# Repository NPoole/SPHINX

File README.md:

# SPHINX
Project to reproduce the Russian СФИНКС home computer concept

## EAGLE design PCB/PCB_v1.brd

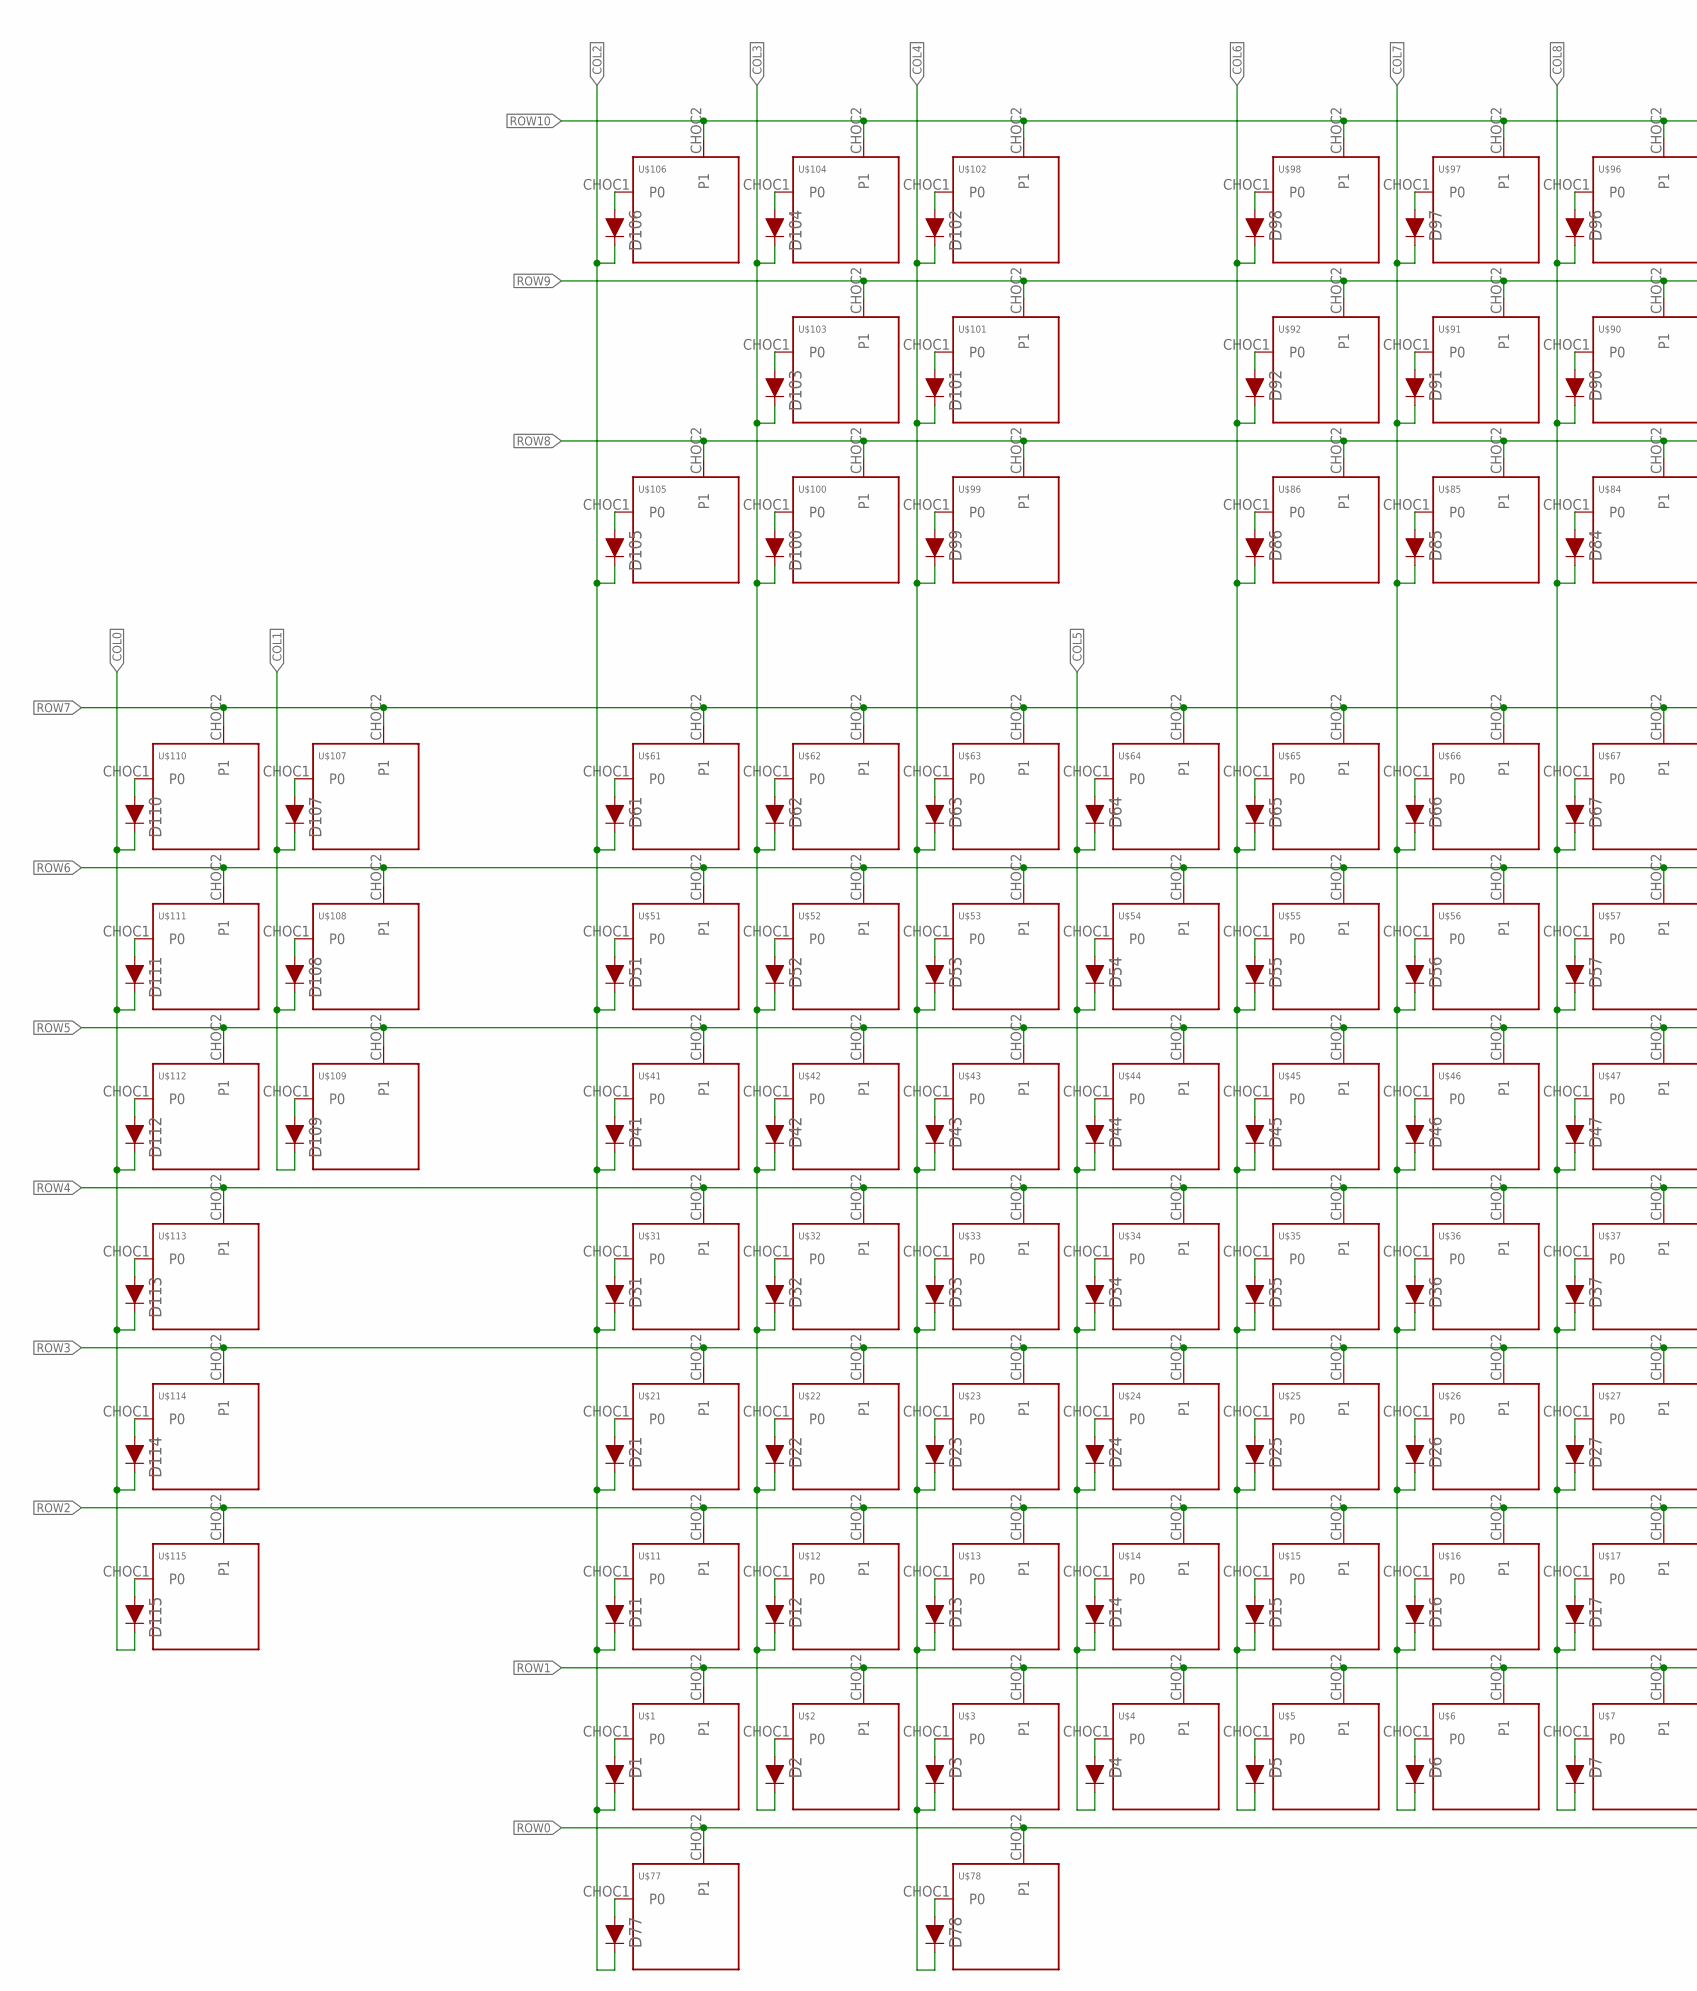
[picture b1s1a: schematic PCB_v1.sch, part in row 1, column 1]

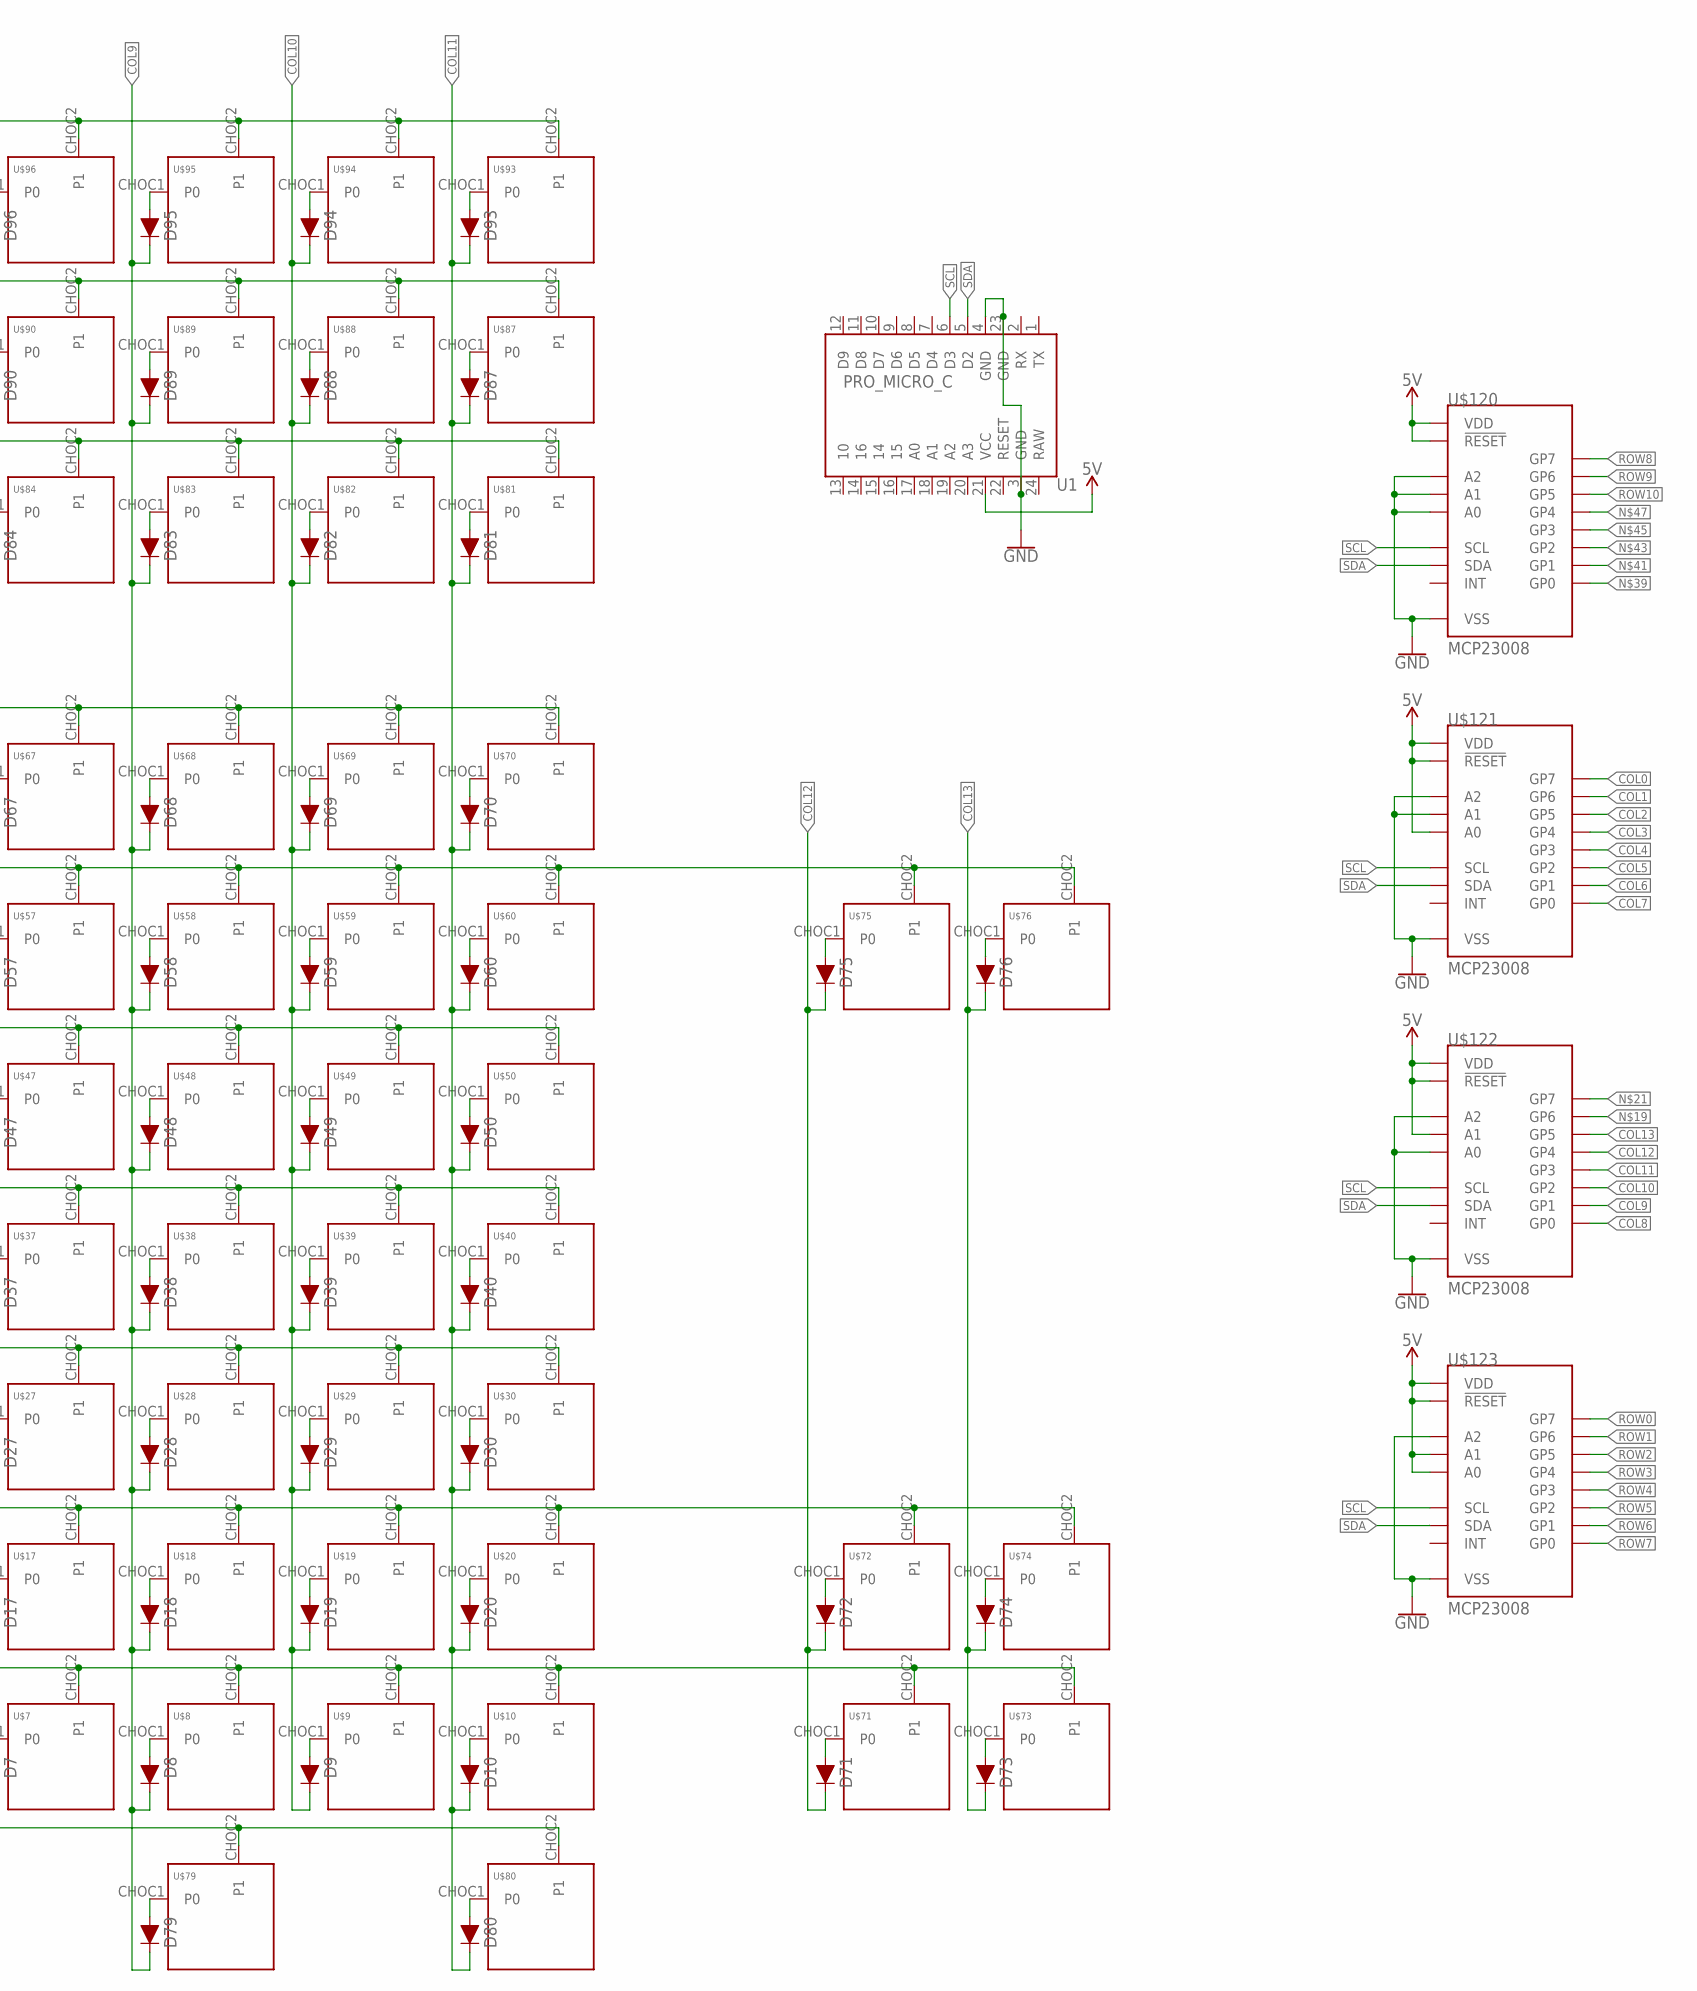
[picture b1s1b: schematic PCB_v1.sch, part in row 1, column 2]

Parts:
D1, D2, D3, D4, D5, D6, D7, D8, D9, D10, D11, D12, D13, D14, D15, D16, D17, D18, D19, D20, D21, D22, D23, D24, D25, D26, D27, D28, D29, D30, D31, D32, D33, D34, D35, D36, D37, D38, D39, D40, D41, D42, D43, D44, D45, D46, D47, D48, D49, D50, D51, D52, D53, D54, D55, D56, D57, D58, D59, D60, D61, D62, D63, D64, D65, D66, D67, D68, D69, D70, D71, D72, D73, D74, D75, D76, D77, D78, D79, D80, D81, D82, D83, D84, D85, D86, D87, D88, D89, D90, D91, D92, D93, D94, D95, D96, D97, D98, D99, D100, D101, D102, D103, D104, D105, D106, D107, D108, D109, D110, D111, D112, D113, D114, D115: 200mA/100V/1V; DIODE-1N4148-KIT
U1: PRO_MICRO_C
U$1, U$2, U$3, U$4, U$5, U$6, U$7, U$8, U$9, U$10, U$11, U$12, U$13, U$14, U$15, U$16, U$17, U$18, U$19, U$20, U$21, U$22, U$23, U$24, U$25, U$26, U$27, U$28, U$29, U$30, U$31, U$32, U$33, U$34, U$35, U$36, U$37, U$38, U$39, U$40, U$41, U$42, U$43, U$44, U$45, U$46, U$47, U$48, U$49, U$50, U$51, U$52, U$53, U$54, U$55, U$56, U$57, U$58, U$59, U$60, U$61, U$62, U$63, U$64, U$65, U$66, U$67, U$68, U$69, U$70, U$71, U$72, U$73, U$74, U$75, U$76, U$77, U$78, U$79, U$80, U$81, U$82, U$83, U$84, U$85, U$86, U$87, U$88, U$89, U$90, U$91, U$92, U$93, U$94, U$95, U$96, U$97, U$98, U$99, U$100, U$101, U$102, U$103, U$104, U$105, U$106, U$107, U$108, U$109, U$110, U$111, U$112, U$113, U$114, U$115: KEYSWITCH-PLAIN-CHOC-1U; CHOC-1U
U$120, U$121, U$122, U$123: MCP23008; DIP18

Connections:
5V: U1.21 (VCC), U$120.6 (!RESET), U$120.18 (VDD), U$121.5 (A0), U$121.6 (!RESET), U$121.18 (VDD), U$122.4 (A1), U$122.6 (!RESET), U$122.18 (VDD), U$123.4 (A1), U$123.5 (A0), U$123.6 (!RESET), U$123.18 (VDD)
COL0: D110.C, D111.C, D112.C, D113.C, D114.C, D115.C, U$121.17 (GP7)
COL1: D107.C, D108.C, D109.C, U$121.16 (GP6)
COL2: D1.C, D11.C, D21.C, D31.C, D41.C, D51.C, D61.C, D77.C, D105.C, D106.C, U$121.15 (GP5)
COL3: D2.C, D12.C, D22.C, D32.C, D42.C, D52.C, D62.C, D100.C, D103.C, D104.C, U$121.14 (GP4)
COL4: D3.C, D13.C, D23.C, D33.C, D43.C, D53.C, D63.C, D78.C, D99.C, D101.C, D102.C, U$121.13 (GP3)
COL5: D4.C, D14.C, D24.C, D34.C, D44.C, D54.C, D64.C, U$121.12 (GP2)
COL6: D5.C, D15.C, D25.C, D35.C, D45.C, D55.C, D65.C, D86.C, D92.C, D98.C, U$121.11 (GP1)
COL7: D6.C, D16.C, D26.C, D36.C, D46.C, D56.C, D66.C, D85.C, D91.C, D97.C, U$121.10 (GP0)
COL8: D7.C, D17.C, D27.C, D37.C, D47.C, D57.C, D67.C, D84.C, D90.C, D96.C, U$122.10 (GP0)
COL9: D8.C, D18.C, D28.C, D38.C, D48.C, D58.C, D68.C, D79.C, D83.C, D89.C, D95.C, U$122.11 (GP1)
COL10: D9.C, D19.C, D29.C, D39.C, D49.C, D59.C, D69.C, D82.C, D88.C, D94.C, U$122.12 (GP2)
COL11: D10.C, D20.C, D30.C, D40.C, D50.C, D60.C, D70.C, D80.C, D81.C, D87.C, D93.C, U$122.13 (GP3)
COL12: D71.C, D72.C, D75.C, U$122.14 (GP4)
COL13: D73.C, D74.C, D76.C, U$122.15 (GP5)
GND: U1.3 (GND), U1.4 (GND), U1.23 (GND), U$120.3 (A2), U$120.4 (A1), U$120.5 (A0), U$120.9 (VSS), U$121.3 (A2), U$121.4 (A1), U$121.9 (VSS), U$122.3 (A2), U$122.5 (A0), U$122.9 (VSS), U$123.3 (A2), U$123.9 (VSS)
unnamed: D77.A, U$77.CHOC1 (P0)
unnamed: D78.A, U$78.CHOC1 (P0)
unnamed: D79.A, U$79.CHOC1 (P0)
unnamed: D80.A, U$80.CHOC1 (P0)
unnamed: D73.A, U$73.CHOC1 (P0)
unnamed: D71.A, U$71.CHOC1 (P0)
unnamed: D72.A, U$72.CHOC1 (P0)
unnamed: D74.A, U$74.CHOC1 (P0)
unnamed: D20.A, U$20.CHOC1 (P0)
unnamed: D10.A, U$10.CHOC1 (P0)
unnamed: D9.A, U$9.CHOC1 (P0)
unnamed: D8.A, U$8.CHOC1 (P0)
unnamed: D7.A, U$7.CHOC1 (P0)
unnamed: D17.A, U$17.CHOC1 (P0)
unnamed: D18.A, U$18.CHOC1 (P0)
unnamed: D19.A, U$19.CHOC1 (P0)
unnamed: D16.A, U$16.CHOC1 (P0)
unnamed: D6.A, U$6.CHOC1 (P0)
unnamed: D5.A, U$5.CHOC1 (P0)
unnamed: D4.A, U$4.CHOC1 (P0)
unnamed: D3.A, U$3.CHOC1 (P0)
unnamed: D15.A, U$15.CHOC1 (P0)
unnamed: D14.A, U$14.CHOC1 (P0)
unnamed: D13.A, U$13.CHOC1 (P0)
unnamed: D12.A, U$12.CHOC1 (P0)
unnamed: D2.A, U$2.CHOC1 (P0)
unnamed: D1.A, U$1.CHOC1 (P0)
unnamed: D11.A, U$11.CHOC1 (P0)
unnamed: D50.A, U$50.CHOC1 (P0)
unnamed: D40.A, U$40.CHOC1 (P0)
unnamed: D30.A, U$30.CHOC1 (P0)
unnamed: D29.A, U$29.CHOC1 (P0)
unnamed: D39.A, U$39.CHOC1 (P0)
unnamed: D49.A, U$49.CHOC1 (P0)
unnamed: D48.A, U$48.CHOC1 (P0)
unnamed: D38.A, U$38.CHOC1 (P0)
unnamed: D28.A, U$28.CHOC1 (P0)
unnamed: D27.A, U$27.CHOC1 (P0)
unnamed: D37.A, U$37.CHOC1 (P0)
unnamed: D47.A, U$47.CHOC1 (P0)
unnamed: D46.A, U$46.CHOC1 (P0)
unnamed: D36.A, U$36.CHOC1 (P0)
unnamed: D26.A, U$26.CHOC1 (P0)
unnamed: D25.A, U$25.CHOC1 (P0)
unnamed: D35.A, U$35.CHOC1 (P0)
unnamed: D45.A, U$45.CHOC1 (P0)
unnamed: D44.A, U$44.CHOC1 (P0)
unnamed: D43.A, U$43.CHOC1 (P0)
unnamed: D42.A, U$42.CHOC1 (P0)
unnamed: D41.A, U$41.CHOC1 (P0)
unnamed: D31.A, U$31.CHOC1 (P0)
unnamed: D32.A, U$32.CHOC1 (P0)
unnamed: D33.A, U$33.CHOC1 (P0)
unnamed: D34.A, U$34.CHOC1 (P0)
unnamed: D24.A, U$24.CHOC1 (P0)
unnamed: D23.A, U$23.CHOC1 (P0)
unnamed: D22.A, U$22.CHOC1 (P0)
unnamed: D21.A, U$21.CHOC1 (P0)
unnamed: D70.A, U$70.CHOC1 (P0)
unnamed: D69.A, U$69.CHOC1 (P0)
unnamed: D68.A, U$68.CHOC1 (P0)
unnamed: D67.A, U$67.CHOC1 (P0)
unnamed: D66.A, U$66.CHOC1 (P0)
unnamed: D56.A, U$56.CHOC1 (P0)
unnamed: D57.A, U$57.CHOC1 (P0)
unnamed: D58.A, U$58.CHOC1 (P0)
unnamed: D59.A, U$59.CHOC1 (P0)
unnamed: D60.A, U$60.CHOC1 (P0)
unnamed: D65.A, U$65.CHOC1 (P0)
unnamed: D55.A, U$55.CHOC1 (P0)
unnamed: D54.A, U$54.CHOC1 (P0)
unnamed: D64.A, U$64.CHOC1 (P0)
unnamed: D63.A, U$63.CHOC1 (P0)
unnamed: D53.A, U$53.CHOC1 (P0)
unnamed: D52.A, U$52.CHOC1 (P0)
unnamed: D62.A, U$62.CHOC1 (P0)
unnamed: D61.A, U$61.CHOC1 (P0)
unnamed: D51.A, U$51.CHOC1 (P0)
unnamed: D107.A, U$107.CHOC1 (P0)
unnamed: D108.A, U$108.CHOC1 (P0)
unnamed: D111.A, U$111.CHOC1 (P0)
unnamed: D110.A, U$110.CHOC1 (P0)
unnamed: D109.A, U$109.CHOC1 (P0)
unnamed: D112.A, U$112.CHOC1 (P0)
unnamed: D113.A, U$113.CHOC1 (P0)
unnamed: D114.A, U$114.CHOC1 (P0)
unnamed: D115.A, U$115.CHOC1 (P0)
unnamed: D76.A, U$76.CHOC1 (P0)
unnamed: D75.A, U$75.CHOC1 (P0)
unnamed: D93.A, U$93.CHOC1 (P0)
unnamed: D87.A, U$87.CHOC1 (P0)
unnamed: D81.A, U$81.CHOC1 (P0)
unnamed: D82.A, U$82.CHOC1 (P0)
unnamed: D88.A, U$88.CHOC1 (P0)
unnamed: D94.A, U$94.CHOC1 (P0)
unnamed: D95.A, U$95.CHOC1 (P0)
unnamed: D89.A, U$89.CHOC1 (P0)
unnamed: D83.A, U$83.CHOC1 (P0)
unnamed: D84.A, U$84.CHOC1 (P0)
unnamed: D90.A, U$90.CHOC1 (P0)
unnamed: D96.A, U$96.CHOC1 (P0)
unnamed: D97.A, U$97.CHOC1 (P0)
unnamed: D98.A, U$98.CHOC1 (P0)
unnamed: D92.A, U$92.CHOC1 (P0)
unnamed: D91.A, U$91.CHOC1 (P0)
unnamed: D85.A, U$85.CHOC1 (P0)
unnamed: D86.A, U$86.CHOC1 (P0)
unnamed: D102.A, U$102.CHOC1 (P0)
unnamed: D104.A, U$104.CHOC1 (P0)
unnamed: D106.A, U$106.CHOC1 (P0)
unnamed: D103.A, U$103.CHOC1 (P0)
unnamed: D101.A, U$101.CHOC1 (P0)
unnamed: D99.A, U$99.CHOC1 (P0)
unnamed: D100.A, U$100.CHOC1 (P0)
unnamed: D105.A, U$105.CHOC1 (P0)
ROW0: U$77.CHOC2 (P1), U$78.CHOC2 (P1), U$79.CHOC2 (P1), U$80.CHOC2 (P1), U$123.17 (GP7)
ROW1: U$1.CHOC2 (P1), U$2.CHOC2 (P1), U$3.CHOC2 (P1), U$4.CHOC2 (P1), U$5.CHOC2 (P1), U$6.CHOC2 (P1), U$7.CHOC2 (P1), U$8.CHOC2 (P1), U$9.CHOC2 (P1), U$10.CHOC2 (P1), U$71.CHOC2 (P1), U$73.CHOC2 (P1), U$123.16 (GP6)
ROW2: U$11.CHOC2 (P1), U$12.CHOC2 (P1), U$13.CHOC2 (P1), U$14.CHOC2 (P1), U$15.CHOC2 (P1), U$16.CHOC2 (P1), U$17.CHOC2 (P1), U$18.CHOC2 (P1), U$19.CHOC2 (P1), U$20.CHOC2 (P1), U$72.CHOC2 (P1), U$74.CHOC2 (P1), U$115.CHOC2 (P1), U$123.15 (GP5)
ROW3: U$21.CHOC2 (P1), U$22.CHOC2 (P1), U$23.CHOC2 (P1), U$24.CHOC2 (P1), U$25.CHOC2 (P1), U$26.CHOC2 (P1), U$27.CHOC2 (P1), U$28.CHOC2 (P1), U$29.CHOC2 (P1), U$30.CHOC2 (P1), U$114.CHOC2 (P1), U$123.14 (GP4)
ROW4: U$31.CHOC2 (P1), U$32.CHOC2 (P1), U$33.CHOC2 (P1), U$34.CHOC2 (P1), U$35.CHOC2 (P1), U$36.CHOC2 (P1), U$37.CHOC2 (P1), U$38.CHOC2 (P1), U$39.CHOC2 (P1), U$40.CHOC2 (P1), U$113.CHOC2 (P1), U$123.13 (GP3)
ROW5: U$41.CHOC2 (P1), U$42.CHOC2 (P1), U$43.CHOC2 (P1), U$44.CHOC2 (P1), U$45.CHOC2 (P1), U$46.CHOC2 (P1), U$47.CHOC2 (P1), U$48.CHOC2 (P1), U$49.CHOC2 (P1), U$50.CHOC2 (P1), U$109.CHOC2 (P1), U$112.CHOC2 (P1), U$123.12 (GP2)
ROW6: U$51.CHOC2 (P1), U$52.CHOC2 (P1), U$53.CHOC2 (P1), U$54.CHOC2 (P1), U$55.CHOC2 (P1), U$56.CHOC2 (P1), U$57.CHOC2 (P1), U$58.CHOC2 (P1), U$59.CHOC2 (P1), U$60.CHOC2 (P1), U$75.CHOC2 (P1), U$76.CHOC2 (P1), U$108.CHOC2 (P1), U$111.CHOC2 (P1), U$123.11 (GP1)
ROW7: U$61.CHOC2 (P1), U$62.CHOC2 (P1), U$63.CHOC2 (P1), U$64.CHOC2 (P1), U$65.CHOC2 (P1), U$66.CHOC2 (P1), U$67.CHOC2 (P1), U$68.CHOC2 (P1), U$69.CHOC2 (P1), U$70.CHOC2 (P1), U$107.CHOC2 (P1), U$110.CHOC2 (P1), U$123.10 (GP0)
ROW8: U$81.CHOC2 (P1), U$82.CHOC2 (P1), U$83.CHOC2 (P1), U$84.CHOC2 (P1), U$85.CHOC2 (P1), U$86.CHOC2 (P1), U$99.CHOC2 (P1), U$100.CHOC2 (P1), U$105.CHOC2 (P1), U$120.17 (GP7)
ROW9: U$87.CHOC2 (P1), U$88.CHOC2 (P1), U$89.CHOC2 (P1), U$90.CHOC2 (P1), U$91.CHOC2 (P1), U$92.CHOC2 (P1), U$101.CHOC2 (P1), U$103.CHOC2 (P1), U$120.16 (GP6)
ROW10: U$93.CHOC2 (P1), U$94.CHOC2 (P1), U$95.CHOC2 (P1), U$96.CHOC2 (P1), U$97.CHOC2 (P1), U$98.CHOC2 (P1), U$102.CHOC2 (P1), U$104.CHOC2 (P1), U$106.CHOC2 (P1), U$120.15 (GP5)
SCL: U1.6 (D3), U$120.1 (SCL), U$121.1 (SCL), U$122.1 (SCL), U$123.1 (SCL)
SDA: U1.5 (D2), U$120.2 (SDA), U$121.2 (SDA), U$122.2 (SDA), U$123.2 (SDA)

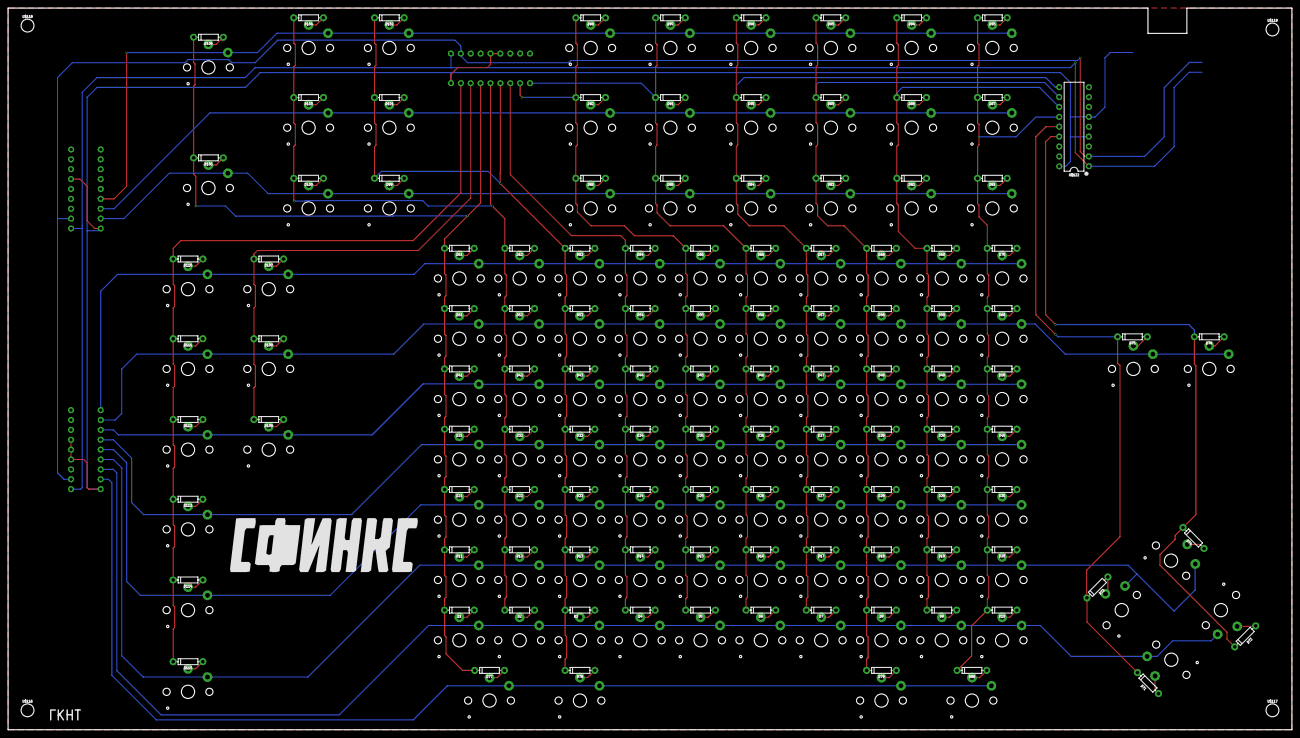
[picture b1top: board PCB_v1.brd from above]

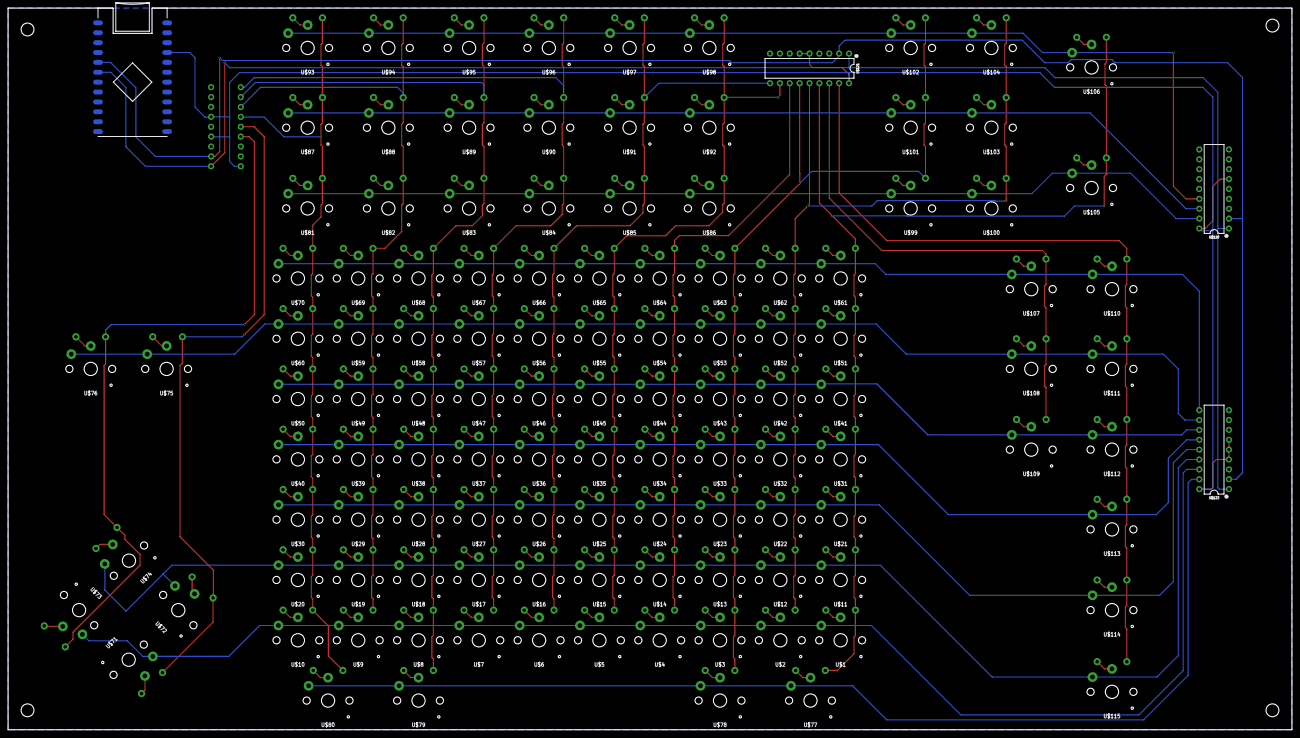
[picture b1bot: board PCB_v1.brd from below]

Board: 2 copper layers, 330.0 x 185.5 mm, 240 parts (4 on the bottom side), 144 nets.

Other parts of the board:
U$116, U$117, U$118, U$119: STAND-OFF
U$124: SPHINX#SVG0

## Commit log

2021-11-16 Finally organizing this material

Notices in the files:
parts and their libraries:
SparkFun-DiscreteSemi: Licensing: Creative Commons ShareAlike 4.0 International - https://creativecommons.org/licenses/by-sa/4.0
